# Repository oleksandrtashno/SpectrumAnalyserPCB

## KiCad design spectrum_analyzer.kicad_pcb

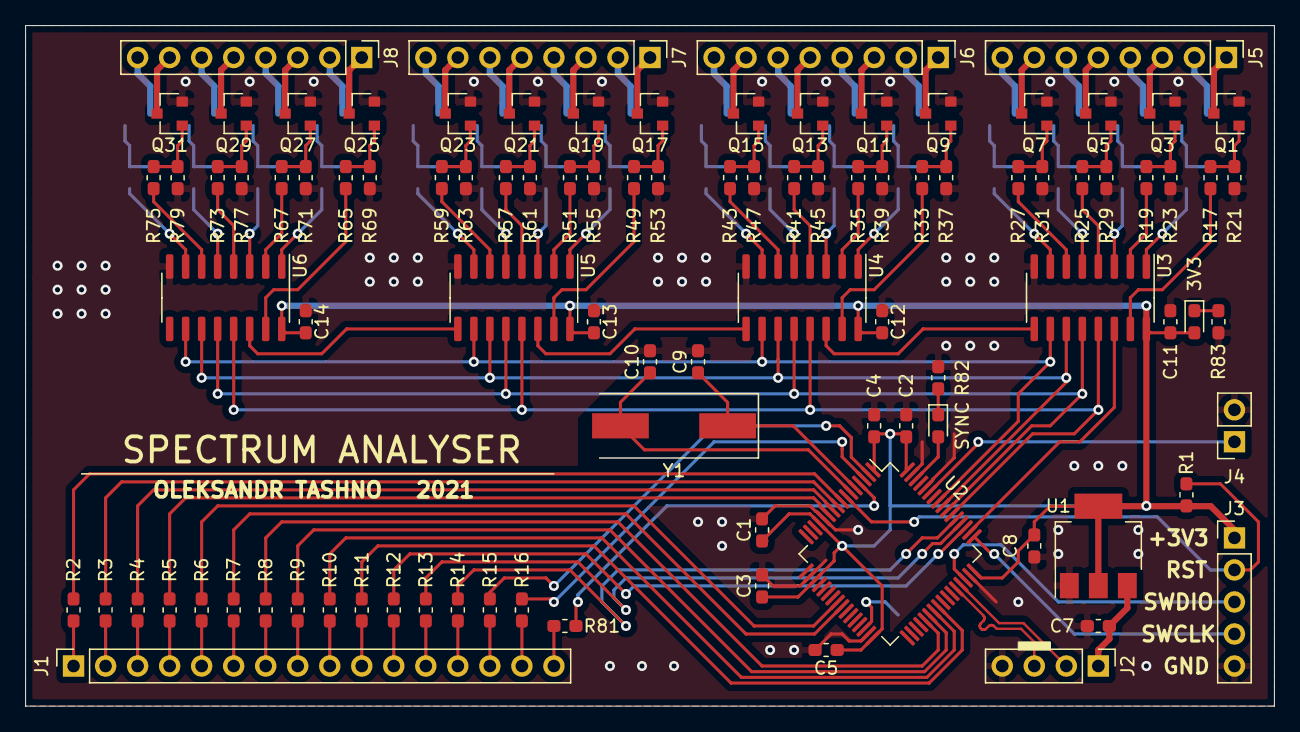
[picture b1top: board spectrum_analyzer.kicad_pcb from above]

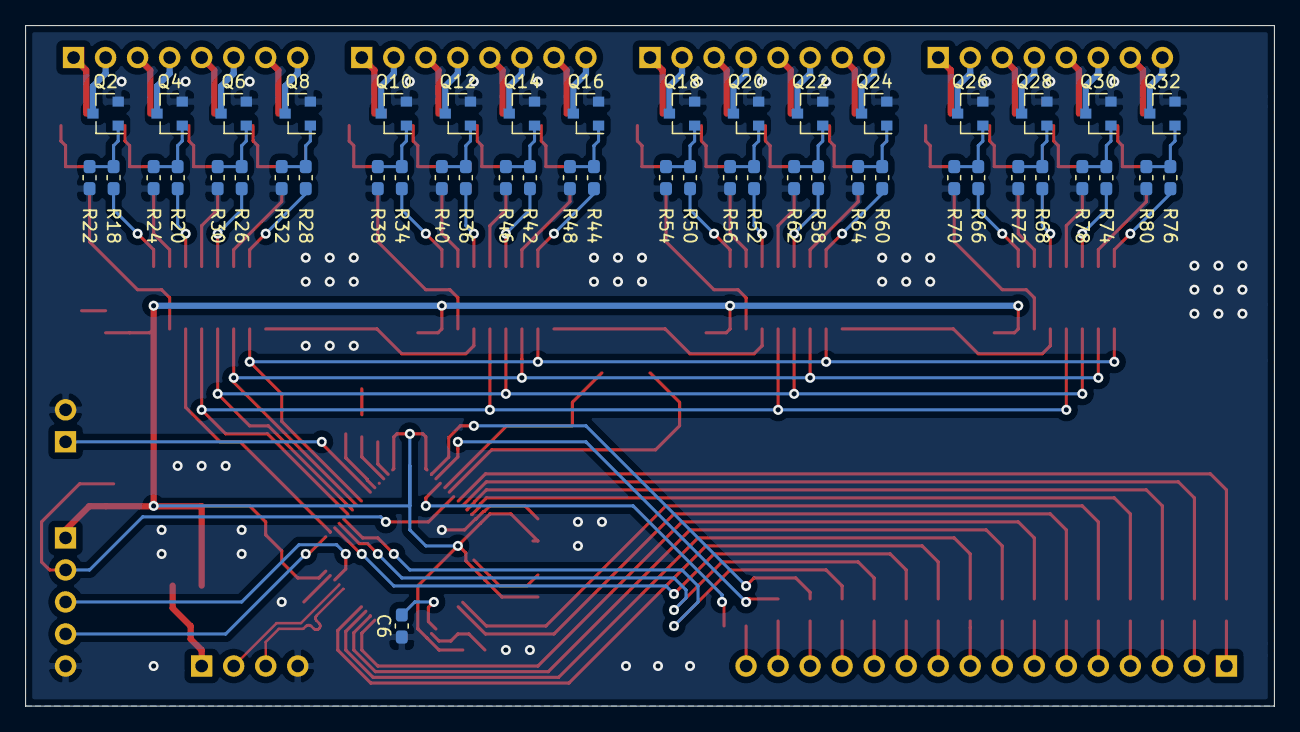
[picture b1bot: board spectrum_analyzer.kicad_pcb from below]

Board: 2 copper layers, 99.1 x 54.0 mm, 146 parts (49 on the bottom side), 151 nets.

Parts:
3V3: LED; LED_0603_1608Metric_Pad1.05x0.95mm_HandSolder
C1, C2, C3, C4, C5, C7, C8, C11, C12, C13, C14: 100nF; C_0603_1608Metric_Pad1.05x0.95mm_HandSolder
C6: 2.2uF; C_0603_1608Metric_Pad1.05x0.95mm_HandSolder
C9, C10: 18p; C_0603_1608Metric_Pad1.05x0.95mm_HandSolder
J1: Conn_01x16_Male; PinSocket_1x16_P2.54mm_Vertical
J2: USB; PinHeader_1x04_P2.54mm_Vertical
J3: ST-LINK; PinHeader_1x05_P2.54mm_Vertical
J4: Conn_01x02_Male; PinSocket_1x02_P2.54mm_Vertical
J5, J6, J7, J8: Conn_01x08_Male; PinHeader_1x08_P2.54mm_Vertical
Q1, Q2, Q3, Q4, Q5, Q6, Q7, Q8, Q9, Q10, Q11, Q12, Q13, Q14, Q15, Q16, Q17, Q18, Q19, Q20, Q21, Q22, Q23, Q24, Q25, Q26, Q27, Q28, Q29, Q30, Q31, Q32: BC817; SOT-23
R1, R82, R83: 10K; R_0603_1608Metric_Pad1.05x0.95mm_HandSolder
R2, R3, R4, R5, R6, R7, R8, R9, R10, R11, R12, R13, R14, R15, R16, R81: 62; R_0603_1608Metric_Pad1.05x0.95mm_HandSolder
R17, R18, R19, R20, R25, R26, R27, R28, R33, R34, R35, R36, R41, R42, R43, R44, R49, R50, R51, R52, R57, R58, R59, R60, R65, R66, R67, R68, R73, R74, R75, R76: 1k; R_0603_1608Metric_Pad1.05x0.95mm_HandSolder
R21, R22, R23, R24, R29, R30, R31, R32, R37, R38, R39, R40, R45, R46, R47, R48, R53, R54, R55, R56, R61, R62, R63, R64, R69, R70, R71, R72, R77, R78, R79, R80: 27k; R_0603_1608Metric_Pad1.05x0.95mm_HandSolder
SYNC: LED; LED_0603_1608Metric_Pad1.05x0.95mm_HandSolder
U1: AMS1117-3.3; SOT-223-3_TabPin2
U2: STM32F446RCTx; LQFP-64_10x10mm_P0.5mm
U3, U4, U5, U6: 74HC595; SOIC-16_3.9x9.9mm_P1.27mm
Y1: Crystal; Crystal_SMD_HC49-SD

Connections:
+3V3: 3V3.2, C1.1, C2.1, C3.1, C4.1, C5.1, C8.1, C11.1, C12.1, C13.1, C14.1, J3.1, R1.2, U1.2, U2.1, U2.13, U2.19, U2.32, U2.48, U2.64, U3.16, U4.16, U5.16, U6.16
+5V: C7.1, J2.1, U1.3
/Sheet60279AD9/COL0: J5.1, Q1.3
/Sheet60279AD9/COL1: J5.2, Q2.3
/Sheet60279AD9/COL2: J5.3, Q3.3
/Sheet60279AD9/COL3: J5.4, Q4.3
/Sheet60279AD9/COL4: J5.5, Q5.3
/Sheet60279AD9/COL5: J5.6, Q6.3
/Sheet60279AD9/COL6: J5.7, Q7.3
/Sheet60279AD9/COL7: J5.8, Q8.3
/Sheet60279AD9/Q0: R17.1, U3.15
/Sheet60279AD9/Q1: R18.1, U3.1
/Sheet60279AD9/Q2: R19.1, U3.2
/Sheet60279AD9/Q3: R20.1, U3.3
/Sheet60279AD9/Q4: R25.1, U3.4
/Sheet60279AD9/Q5: R26.1, U3.5
/Sheet60279AD9/Q6: R27.1, U3.6
/Sheet60279AD9/Q7: R28.1, U3.7
/sheet602AADF8/COL0: J6.1, Q9.3
/sheet602AADF8/COL1: J6.2, Q10.3
/sheet602AADF8/COL2: J6.3, Q11.3
/sheet602AADF8/COL3: J6.4, Q12.3
/sheet602AADF8/COL4: J6.5, Q13.3
/sheet602AADF8/COL5: J6.6, Q14.3
/sheet602AADF8/COL6: J6.7, Q15.3
/sheet602AADF8/COL7: J6.8, Q16.3
/sheet602AADF8/Q0: R33.1, U4.15
/sheet602AADF8/Q1: R34.1, U4.1
/sheet602AADF8/Q2: R35.1, U4.2
/sheet602AADF8/Q3: R36.1, U4.3
/sheet602AADF8/Q4: R41.1, U4.4
/sheet602AADF8/Q5: R42.1, U4.5
/sheet602AADF8/Q6: R43.1, U4.6
/sheet602AADF8/Q7: R44.1, U4.7
/sheet602AADF8/SIN: U3.9, U4.14
/sheet602ABB8A/COL0: J7.1, Q17.3
/sheet602ABB8A/COL1: J7.2, Q18.3
/sheet602ABB8A/COL2: J7.3, Q19.3
/sheet602ABB8A/COL3: J7.4, Q20.3
/sheet602ABB8A/COL4: J7.5, Q21.3
/sheet602ABB8A/COL5: J7.6, Q22.3
/sheet602ABB8A/COL6: J7.7, Q23.3
/sheet602ABB8A/COL7: J7.8, Q24.3
/sheet602ABB8A/Q0: R49.1, U5.15
/sheet602ABB8A/Q1: R50.1, U5.1
/sheet602ABB8A/Q2: R51.1, U5.2
/sheet602ABB8A/Q3: R52.1, U5.3
/sheet602ABB8A/Q4: R57.1, U5.4
/sheet602ABB8A/Q5: R58.1, U5.5
/sheet602ABB8A/Q6: R59.1, U5.6
/sheet602ABB8A/Q7: R60.1, U5.7
/sheet602ABB8A/SIN: U4.9, U5.14
/sheet602AC499/COL0: J8.1, Q25.3
/sheet602AC499/COL1: J8.2, Q26.3
/sheet602AC499/COL2: J8.3, Q27.3
/sheet602AC499/COL3: J8.4, Q28.3
/sheet602AC499/COL4: J8.5, Q29.3
/sheet602AC499/COL5: J8.6, Q30.3
/sheet602AC499/COL6: J8.7, Q31.3
/sheet602AC499/COL7: J8.8, Q32.3
/sheet602AC499/Q0: R65.1, U6.15
/sheet602AC499/Q1: R66.1, U6.1
/sheet602AC499/Q2: R67.1, U6.2
/sheet602AC499/Q3: R68.1, U6.3
/sheet602AC499/Q4: R73.1, U6.4
/sheet602AC499/Q5: R74.1, U6.5
/sheet602AC499/Q6: R75.1, U6.6
/sheet602AC499/Q7: R76.1, U6.7
/sheet602AC499/SIN: U5.9, U6.14
GND: C1.2, C2.2, C3.2, C4.2, C5.2, C6.1, C7.2, C8.2, C9.2, C10.2, C11.2, C12.2, C13.2, C14.2, J2.4, J3.5, J4.2, Q1.2, Q2.2, Q3.2, Q4.2, Q5.2, Q6.2, Q7.2, Q8.2, Q9.2, Q10.2, Q11.2, Q12.2, Q13.2, Q14.2, Q15.2, Q16.2, Q17.2, Q18.2, Q19.2, Q20.2, Q21.2, Q22.2, Q23.2, Q24.2, Q25.2, Q26.2, Q27.2, Q28.2, Q29.2, Q30.2, Q31.2, Q32.2, R21.2, R22.2, R23.2, R24.2, R29.2, R30.2, R31.2, R32.2, R37.2, R38.2, R39.2, R40.2, R45.2, R46.2, R47.2, R48.2, R53.2, R54.2, R55.2, R56.2, R61.2, R62.2, R63.2, R64.2, R69.2, R70.2, R71.2, R72.2, R77.2, R78.2, R79.2, R80.2, R82.2, R83.2, U1.1, U2.12, U2.18, U2.31, U2.47, U2.60, U2.63, U3.8, U4.8, U5.8, U6.8
LED: SYNC.2, U2.62
unnamed: C6.2, U2.30
unnamed: C9.1, U2.5, Y1.1
unnamed: C10.1, U2.6, Y1.2
unnamed: R82.1, SYNC.1
unnamed: 3V3.1, R83.1
unnamed: J1.1, R2.2
unnamed: J1.2, R3.2
unnamed: J1.3, R4.2
unnamed: J1.4, R5.2
unnamed: J1.5, R6.2
unnamed: J1.6, R7.2
unnamed: J1.7, R8.2
unnamed: J1.8, R9.2
unnamed: J1.9, R10.2
unnamed: J1.10, R11.2
unnamed: J1.11, R12.2
unnamed: J1.12, R13.2
unnamed: J1.13, R14.2
unnamed: J1.14, R15.2
unnamed: J1.15, R16.2
unnamed: J1.16, R81.2
unnamed: Q1.1, R17.2, R21.1
unnamed: Q2.1, R18.2, R22.1
unnamed: Q3.1, R19.2, R23.1
unnamed: Q4.1, R20.2, R24.1
unnamed: Q5.1, R25.2, R29.1
unnamed: Q6.1, R26.2, R30.1
unnamed: Q7.1, R27.2, R31.1
unnamed: Q8.1, R28.2, R32.1
unnamed: Q9.1, R33.2, R37.1
unnamed: Q10.1, R34.2, R38.1
unnamed: Q11.1, R35.2, R39.1
unnamed: Q12.1, R36.2, R40.1
unnamed: Q13.1, R41.2, R45.1
unnamed: Q14.1, R42.2, R46.1
unnamed: Q15.1, R43.2, R47.1
unnamed: Q16.1, R44.2, R48.1
unnamed: Q17.1, R49.2, R53.1
unnamed: Q18.1, R50.2, R54.1
unnamed: Q19.1, R51.2, R55.1
unnamed: Q20.1, R52.2, R56.1
unnamed: Q21.1, R57.2, R61.1
unnamed: Q22.1, R58.2, R62.1
unnamed: Q23.1, R59.2, R63.1
unnamed: Q24.1, R60.2, R64.1
unnamed: Q25.1, R65.2, R69.1
unnamed: Q26.1, R66.2, R70.1
unnamed: Q27.1, R67.2, R71.1
unnamed: Q28.1, R68.2, R72.1
unnamed: Q29.1, R73.2, R77.1
unnamed: Q30.1, R74.2, R78.1
unnamed: Q31.1, R75.2, R79.1
unnamed: Q32.1, R76.2, R80.1
OE: U2.54, U3.13, U4.13, U5.13, U6.13
ROW0: R2.1, U2.8
ROW1: R3.1, U2.9
ROW2: R4.1, U2.10
ROW3: R5.1, U2.11
ROW4: R6.1, U2.24
ROW5: R7.1, U2.25
ROW6: R8.1, U2.37
ROW7: R9.1, U2.38
ROW8: R10.1, U2.39
ROW9: R11.1, U2.40
ROW10: R12.1, U2.51
ROW11: R13.1, U2.52
ROW12: R14.1, U2.53
ROW13: R15.1, U2.2
ROW14: R16.1, U2.3
ROW15: R81.1, U2.4
RST: J3.2, R1.1, U2.7
SHCLK: U2.56, U3.11, U4.11, U5.11, U6.11
SHRST: U2.57, U3.10, U4.10, U5.10, U6.10
SIN: U2.50, U3.14
SPDIFRX: J4.1, U2.59
STORE: U2.55, U3.12, U4.12, U5.12, U6.12
SWCLK: J3.4, U2.49
SWDIO: J3.3, U2.46
USB_D+: J2.2, U2.45
USB_D-: J2.3, U2.44
